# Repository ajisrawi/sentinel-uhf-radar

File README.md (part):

<p align="center">
  <picture>
    <source media="(prefers-color-scheme: dark)" srcset="docs/assets/logo-dark.svg">
    
  </picture>
</p>

<p align="center">
  <b>A complete reference design for a two-face UHF early-warning phased-array radar</b><br>
  system sizing · antenna design and EM simulation · seven KiCad PCB projects · site visualisation
</p>

<p align="center">
  
  <br><sub>AI visualisation (Pixelcut / Nano Banana 2.1) generated from the project's Blender model. Site details are illustrative.</sub>
</p>

---

## Contents

- [What this is](#what-this-is)
- [Key numbers](#key-numbers)
- [Architecture](#architecture)
- [System design](#system-design)
- [Antenna and EM simulation](#antenna-and-em-simulation)
- [Electronics: seven custom boards](#electronics-seven-custom-boards)
- [Site and building](#site-and-building)
- [Cost estimate](#cost-estimate)
- [Repository layout](#repository-layout)
- [Reproduce everything](#reproduce-everything)
- [Verification status and known gaps](#verification-status-and-known-gaps)
- [Notes](#notes)

## What this is

SENTINEL-UHF is an engineering reference design for a ground-based early-warning radar in the class of
PAVE PAWS / UEWR. It is built from public radar engineering principles, and every number in it comes from code in
this repository:

- a **system budget** (aperture, power, detection range, search fence, data rates),
- an **antenna element** sized with a **method-of-moments EM solver** written for the project and validated against
  textbook results, including a 61-element mutual-coupling and scan-impedance study,
- **seven complete KiCad 10 projects** covering every custom board in the radar, each with a schematic, PCB, gerbers
  and its own symbol/footprint library,
- a **Blender model** of the site and a photorealistic visualisation.

It is a first-pass design meant for study and as a starting point. It is not a fielded system and nothing here is
released for fabrication.

## Key numbers

| | |
|---|---|
| Band | 420–450 MHz (UHF radiolocation), circular polarisation |
| Faces | 2 × 120° = 240° azimuth, tilted back 20° |
| Aperture | 22 m active circle per face, **2,587 elements** on a 0.41 m triangular lattice |
| Gain / beamwidth | 39.1 dBi / 1.83° at broadside |
| Peak / average RF | **776 kW / 155 kW per face** (300 W GaN per element, 20 % duty) |
| Detection, 10 m² target | **6,301 km** broadside · 5,951 km at 30° · 3,855 km at 60° (incl. EM mismatch loss) |
| Search fence | 135 beams over 120° × 3°, 10.8 s frame |
| Digital back end | 324 RFSoC tiles per face, 1.03 Tb/s element data → 6.4 Gb/s after beamforming |
| Site prime power | 1.45 MW |

## Architecture

```mermaid
flowchart LR
    A["Crossed-dipole element<br/>× 2,587 per face"] --- FB["Feed board<br/>hybrid + baluns"]
    FB --- TRM["T/R module<br/>300 W GaN, LNA"]
    TRM --- BP["Tile backplane<br/>8 slots, fused 50 V"]
    BP --- TILE["RFSoC tile<br/>9 RX + 9 TX channels"]
    CAL["Calibration network"] --- TRM
    CAL --- TILE
    PSU["Subarray PSU<br/>380 V → 50 V"] --- BP
    CLK["Clock & timing<br/>122.88 MHz, SYSREF, PPS"] --- TILE
    TILE -- "QSFP28 4×25 Gb/s" --> BF["Face beamformer<br/>16 receive beams"]
    BF --> SP["Signal processor<br/>pulse compression, Doppler, CFAR"]
    SP --> DP["Data processor<br/>tracking, discrimination, C2"]
```

Every element has its own T/R module and its own ADC/DAC channel. There is no analog beamforming network: beams are
formed digitally, so one face can hold a search fence and track several targets in the same dwell.

## System design

`radar_sizing.py` sizes the radar from first principles (Skolnik, *Radar Handbook*). The lattice spacing is set so
no grating lobes appear out to 60° scan at 450 MHz. The result, 2,587 elements in 22 m, lands very close to the
fielded PAVE PAWS (2,677 positions in 22.1 m), which is a useful sanity check.

| Waveform | Pulse | Bandwidth | Range resolution | Use |
|---|---|---|---|---|
| Long-range search | 16 ms LFM | 100 kHz | 1.5 km | horizon fence |
| Track | 2–8 ms LFM | 1 MHz | 150 m | track updates |
| Discrimination | 0.25–2 ms LFM | 10 MHz | 15 m | object separation |

## Antenna and EM simulation

Each element is a pair of crossed 12 mm aluminium dipoles, **28 cm long, 18 cm above the
face**, combined in a 90° hybrid for circular polarisation.

The element was designed with `antenna/mom.py`, a thin-wire method-of-moments solver written for this project
(rooftop basis functions, Galerkin testing, image theory for the ground plane, delta-gap ports). It reproduces the
textbook half-wave dipole: **84 + j45 Ω and 2.16 dBi** (theory: 2.15 dBi). `antenna/simulate.py` then solves a
**61-element hexagonal patch** (122 ports, 1,830 unknowns) at 420, 435 and 450 MHz to get the full coupling matrix,
the active reflection coefficient versus scan, and the embedded element pattern.

| Result (centre element) | Value |
|---|---|
| Embedded realised gain, broadside | 4.8 dBi (ideal cell 5.9 dBi) |
| Axial ratio, broadside | 1.3 dB |
| Nearest-neighbour coupling | -19.6 dB |
| Worst active reflection, band × ±60° | -3.4 dB |

> **Where it falls short.** The match holds to about −9 dB out to 45° but drops to about −4 dB at 60°, which costs
> about 2.2 dB per pass at the scan edge (already included in the detection numbers). A lattice trade study
> (`antenna/explore.py`) showed a tighter 0.37 m grid gains under 1 dB, which isn't worth 30 % more modules.
> The next step is a wide-angle matching sheet, checked in a full-wave model that includes the balun and feed posts.

## Electronics: seven custom boards

Every custom board is generated from a Python circuit description (`gen_schematic.py` / `gen_design.py`) and checked by
KiCad itself:

1. **ERC**: electrical rules, 0 violations required.
2. **Netlist intent check**: KiCad's extracted netlist is compared pin-for-pin with the intended circuit.
3. **Layout**: a shared placement / fan-out / A* routing engine (`hardware/tools/pcbgen.py`) lays out the board on 4
   layers (signal / solid ground / power + signal / signal), then KiCad DRC checks it, refills the zones and verifies
   parity with the schematic.

| Board | Per face | Role | Parts | Nets | ERC | Netlist | Layout | Size |
|---|---|---|---|---|---|---|---|---|
| **T/R module** | 2,587 | GaN PA chain, receiver, protection, bias, telemetry | 144 | 90 | 0 | ✔ | ✅ DRC clean | 230 × 152 mm |
| **Element feed board** | 2,587 | 90 deg hybrid, matching, baluns into the crossed dipoles | 19 | 11 | 0 | ✔ | ✅ DRC clean | 86 × 56 mm |
| **RFSoC digitiser tile** | 324 | SOM carrier: 9 RX + 9 TX channels, module links, QSFP28 | 118 | 187 | 0 | ✔ | ✅ DRC clean | 320 × 260 mm |
| **Tile backplane** | 324 | 8 module slots, fused 50 V drain bus, point-to-point control | 57 | 59 | 0 | ✔ | ✅ DRC clean | 232 × 112 mm |
| **Subarray power supply** | 324 | 380 V -> 50 V, two 600 W bricks, supervisor, 2.5 mm HV rules | 56 | 38 | 0 | ✔ | ✅ DRC clean | 300 × 185 mm |
| **Calibration network** | 324 | SPDT selector tree + inject/measure switch on the module CAL ports | 37 | 25 | 0 | ✔ | ✅ DRC clean | 120 × 82 mm |
| **Clock & timing** | 41 | PLL-cleaned 122.88 MHz, SYSREF from PPS, LVDS to 8 tiles | 63 | 82 | 0 | ✔ | ✅ DRC clean | 150 × 130 mm |

7 of 7 layouts are DRC-clean with zero unrouted nets.

### T/R module
`hardware/tr_module/` · 2,587 per face · 144 parts · 90 nets · ✅ DRC clean

📄 [Bill of materials (CSV)](hardware/tr_module/export/SENTINEL_TRM_BOM.csv) · [Schematic (PDF)](hardware/tr_module/export/SENTINEL_TRM_schematic.pdf) · [Gerbers](hardware/tr_module/export/gerbers)

GaN driver + 300 W GaN final, drop-in circulator, 30 dB coupler, two-stage PIN/Schottky limiter, LNA (NF 0.5 dB), SAW filter. Hardware sequencing interlock: the drain switch closes only when `TX_EN` AND gate-bias-OK AND MCU-enable. STM32G031 monitors drain current, VSWR, temperature and both gates.

### Element feed board
`hardware/feed_board/` · 2,587 per face · 19 parts · 11 nets · ✅ DRC clean

📄 [Bill of materials (CSV)](hardware/feed_board/export/SENTINEL_FEED_BOM.csv) · [Schematic (PDF)](hardware/feed_board/export/SENTINEL_FEED_schematic.pdf) · [Gerbers](hardware/feed_board/export/gerbers)

3 dB 90° hybrid for circular polarisation, isolated port into a 100 W load, per-dipole matching from the EM model (x: series 11.2 nH; y: shunt 3.9 pF + series 20.7 nH), 1:1 baluns, static-bleed chokes.

### RFSoC digitiser tile
`hardware/rfsoc_tile/` · 324 per face · 118 parts · 187 nets · ✅ DRC clean

📄 [Bill of materials (CSV)](hardware/rfsoc_tile/export/SENTINEL_TILE_BOM.csv) · [Schematic (PDF)](hardware/rfsoc_tile/export/SENTINEL_TILE_schematic.pdf) · [Gerbers](hardware/rfsoc_tile/export/gerbers)

Carrier for a commercial RFSoC system-on-module: 9 receive channels (SMA → 1:2 balun → ADC), 9 transmit channels (DAC → centre-tapped balun → SMA), eight RS-485 module links, clock input, calibration control, QSFP28 (4 × 25 Gb/s) to the beamformer, 12 V → 3.3 V / 3 A buck. Routed with the EasyEDA Pro autorouter (Top / In2 / Bottom, In1 solid GND) and imported back into KiCad (`tools/import_easyeda.py`, `easyeda_routes.json`).

### Tile backplane
`hardware/backplane/` · 324 per face · 57 parts · 59 nets · ✅ DRC clean

📄 [Bill of materials (CSV)](hardware/backplane/export/SENTINEL_BACKPLANE_BOM.csv) · [Schematic (PDF)](hardware/backplane/export/SENTINEL_BACKPLANE_schematic.pdf) · [Gerbers](hardware/backplane/export/gerbers)

Eight module slots. Each gets a 15 A fuse on the 50 V drain bus and a resettable fuse on 12 V aux. All control lines run point-to-point to one 40-pin cable for the tile, so a faulty module cannot disturb its neighbours.

### Subarray power supply
`hardware/psu/` · 324 per face · 56 parts · 38 nets · ✅ DRC clean

📄 [Bill of materials (CSV)](hardware/psu/export/SENTINEL_PSU_BOM.csv) · [Schematic (PDF)](hardware/psu/export/SENTINEL_PSU_schematic.pdf) · [Gerbers](hardware/psu/export/gerbers)

380 VDC → 50 V: two isolated 600 W full bricks (current-shared, OR-ed), NTC inrush limiter with relay bypass, opto-isolated enables, STM32 supervisor, 12 V aux brick. Pulse energy (87 A for 16 ms) comes from a chassis capacitor bank on M6 studs. Primary nets enforce IPC-2221 2.5 mm clearance through KiCad custom rules.

### Calibration network
`hardware/cal_board/` · 324 per face · 37 parts · 25 nets · ✅ DRC clean

📄 [Bill of materials (CSV)](hardware/cal_board/export/SENTINEL_CAL_BOM.csv) · [Schematic (PDF)](hardware/cal_board/export/SENTINEL_CAL_schematic.pdf) · [Gerbers](hardware/cal_board/export/gerbers)

Binary tree of seven SPDT switches (8 → 1, one select bit per level) plus an inject/measure switch, so the tile can inject into or measure every module's coupler port through one common path.

### Clock & timing
`hardware/clock_board/` · 41 per face · 63 parts · 82 nets · ✅ DRC clean

📄 [Bill of materials (CSV)](hardware/clock_board/export/SENTINEL_CLOCK_BOM.csv) · [Schematic (PDF)](hardware/clock_board/export/SENTINEL_CLOCK_schematic.pdf) · [Gerbers](hardware/clock_board/export/gerbers)

Narrow-loop PLL locks a 122.88 MHz VCXO to the site 10 MHz. SYSREF is PPS re-timed by the clean clock in a D flip-flop, so it is phase-aligned on every tile. Six quad LVDS drivers feed 8 tiles.

## Site and building

`render/build_radar.py` builds the site procedurally in Blender. The building is a 48 m equilateral triangle in plan
with its front corner truncated, 32 m high, with both array faces tilted back 20°. Each 33 m face carries a 28 m
octagon of **4,305 crossed-dipole positions**: the 2,587 active elements in the 22 m circle, plus terminated dummy
elements around them. That ratio (60 % active) is close to PAVE PAWS (1,792 of 2,677).

## Cost estimate

Rough order of magnitude for one two-face site, using commercial GaN and RFSoC prices at production volume:

| Item | Basis | $M |
|---|---|---|
| T/R modules | 5,174 × $4–6k | 21–31 |
| RFSoC tiles | 648 × $8–12k | 5–8 |
| Antenna faces | elements, hybrids, ground plane | 5–9 |
| Beamformer and processors | FPGA + GPU | 10–18 |
| Power and cooling | substation, gensets, chillers | 15–25 |
| Building and site works | 32 m structure, security | 40–80 |
| Software | scheduler, tracking, discrimination, C2 | 40–100 |
| Integration, calibration, test | | 20–40 |
| Engineering and program | | 30–60 |
| **Total acquisition** | | **≈ 186–371** |

Equipment alone is about $56–91M. Military-qualified modules ($10–20k each) and software overruns are the biggest
risks. Operation adds roughly $15–25M per year. The > $1 billion figures quoted for fielded radars include decades
of operation, security and program overhead.

## Repository layout

```
radar_sizing.py            system budget (run it first)
antenna/                   MoM solver, element + 61-element array study, lattice trade study, results/
hardware/
  tools/                   schematic writer, PCB engine, KiCad build / ERC / DRC scripts
  tr_module/               T/R module           (KiCad project + generators + gerbers)
  feed_board/              element feed board
  rfsoc_tile/              RFSoC digitiser tile (SOM carrier)
  backplane/               tile backplane
  psu/                     subarray power supply
  cal_board/               calibration network
  clock_board/             clock & timing distribution
render/                    Blender site model and renders
report/                    interactive HTML design report (build_report.py)
docs/                      logo, README figures, generators
```

Each `hardware/<board>/` folder holds `SENTINEL_*.kicad_pro/.kicad_sch/.kicad_pcb`, its `SENTINEL.kicad_sym` /
`SENTINEL.pretty` libraries, `export/` (schematic PDF, grouped BOM CSV, 3D view, gerbers + drill files) and the generators.

## Reproduce everything

Requires Python 3.13 with numpy, scipy, matplotlib, shapely, pillow and PyMuPDF, plus KiCad 10 and Blender 5.2.

```bash
python radar_sizing.py
cd antenna && python simulate.py && cd ..                              # ~8 min
cd hardware/tr_module && python gen_footprints.py && python gen_schematic.py && cd ../..
bash hardware/tools/sch_check.sh hardware/tr_module SENTINEL_TRM        # ERC + netlist check + footprint dump
python hardware/tr_module/pcb_plan.py                                  # place + route (~30-60 min)
bash hardware/tools/pcb_check.sh hardware/tr_module SENTINEL_TRM        # build board, DRC, 3D view, gerbers
bash hardware/tools/export_bom.sh                                      # grouped BOM CSV for every board
# same pattern for the other boards (gen_design.py, then the two check scripts)
blender -b -P render/build_radar.py -- night 64
python report/build_report.py && python docs/make_figures.py && python docs/make_readme.py
```

## Verification status and known gaps

| Item | Status |
|---|---|
| System budget | ✅ cross-checked against public PAVE PAWS figures |
| MoM solver | ✅ validated on the half-wave dipole |
| Element + array EM model | ✅ 61 elements, 3 frequencies, full coupling (thin-wire, infinite ground) |
| Wide-angle match | ⚠️ ~−4 dB at 60°: needs a WAIM sheet and full-wave verification |
| All 7 schematics | ✅ 0 ERC violations, exact netlist match |
| PCB layouts | 7/7 DRC-clean; the rest are being routed |
| Differential pairs | ⚠️ data-converter, LVDS and 25 Gb/s pairs are auto-routed as single nets; need a manual coupled, length-matched pass |
| Pin maps not in the KiCad library | ⚠️ RFSoC SOM connector, PLL and RF modules use this project's own pin maps; map to the chosen parts' datasheets |
| T/R module matching values | ⚠️ first-pass from device models; tune on a load-pull bench |
| Thermal | ⚠️ 45 W average per module on a cold plate; needs CFD and a test article |

## Notes

- **No license.** This repository is published without a license. All rights are reserved by the author; viewing
  is fine, but reuse needs permission.
- Designed with [Claude Code](https://claude.com/claude-code). The radar is a study design built from public
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
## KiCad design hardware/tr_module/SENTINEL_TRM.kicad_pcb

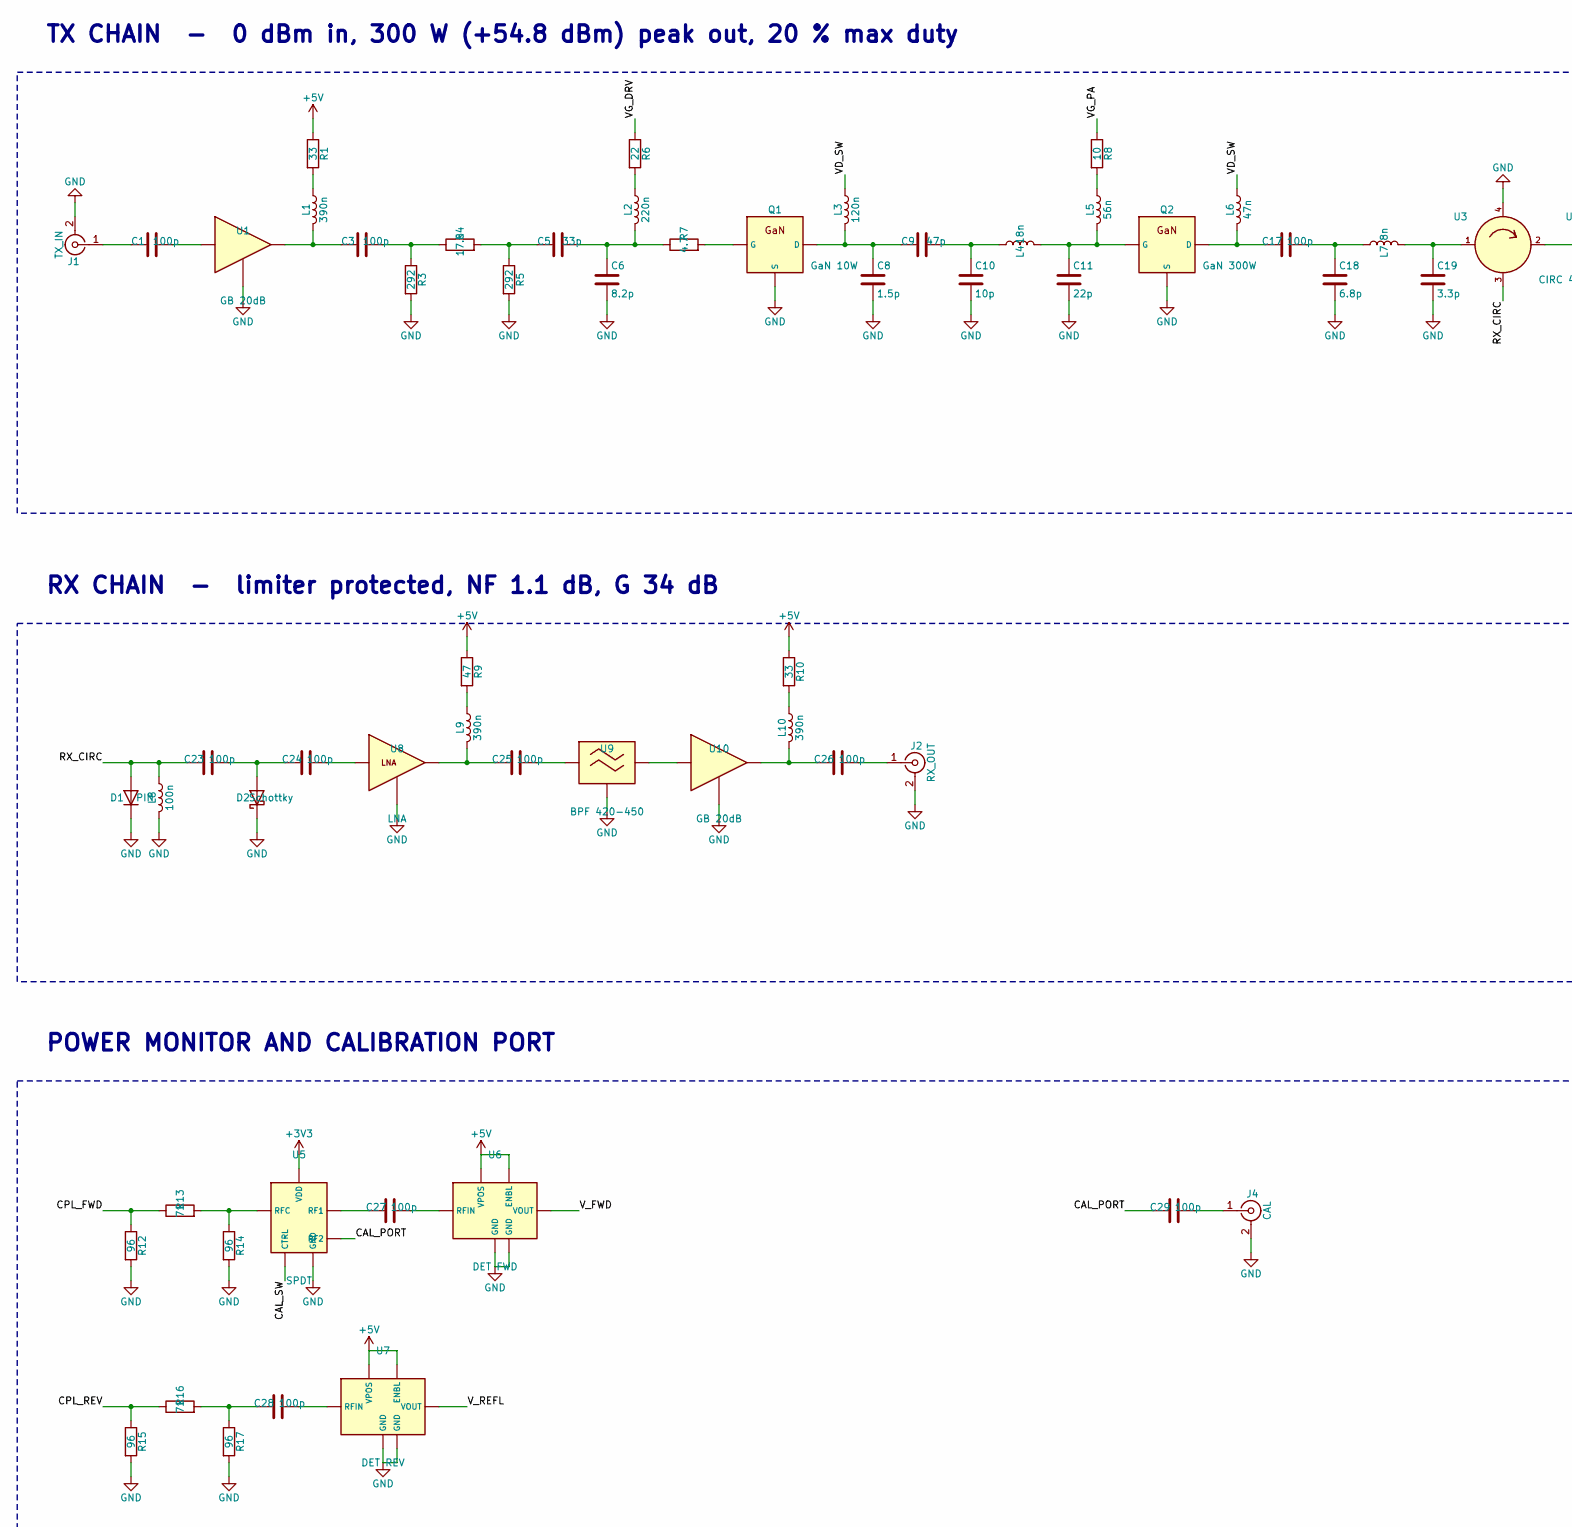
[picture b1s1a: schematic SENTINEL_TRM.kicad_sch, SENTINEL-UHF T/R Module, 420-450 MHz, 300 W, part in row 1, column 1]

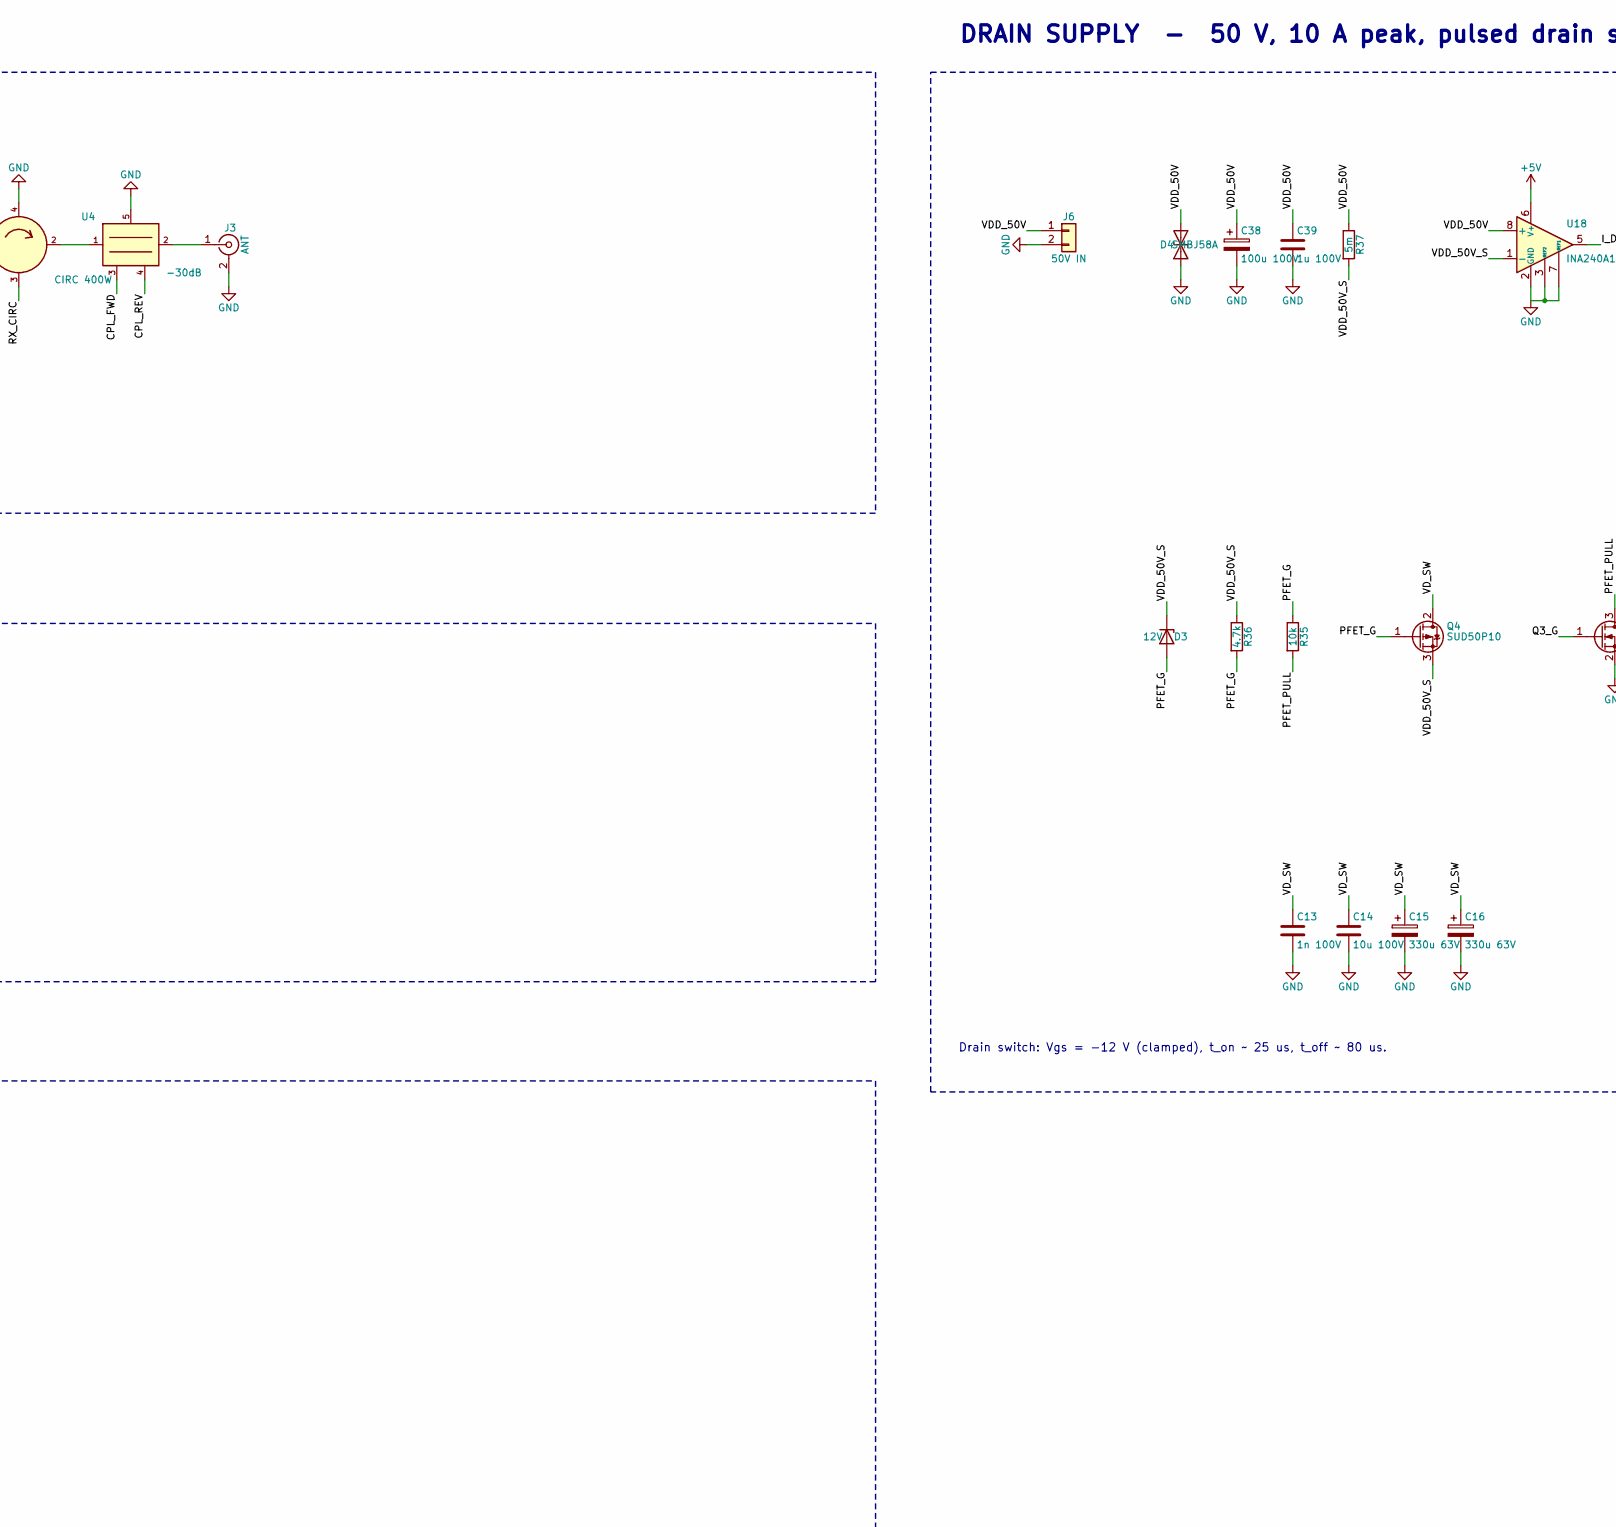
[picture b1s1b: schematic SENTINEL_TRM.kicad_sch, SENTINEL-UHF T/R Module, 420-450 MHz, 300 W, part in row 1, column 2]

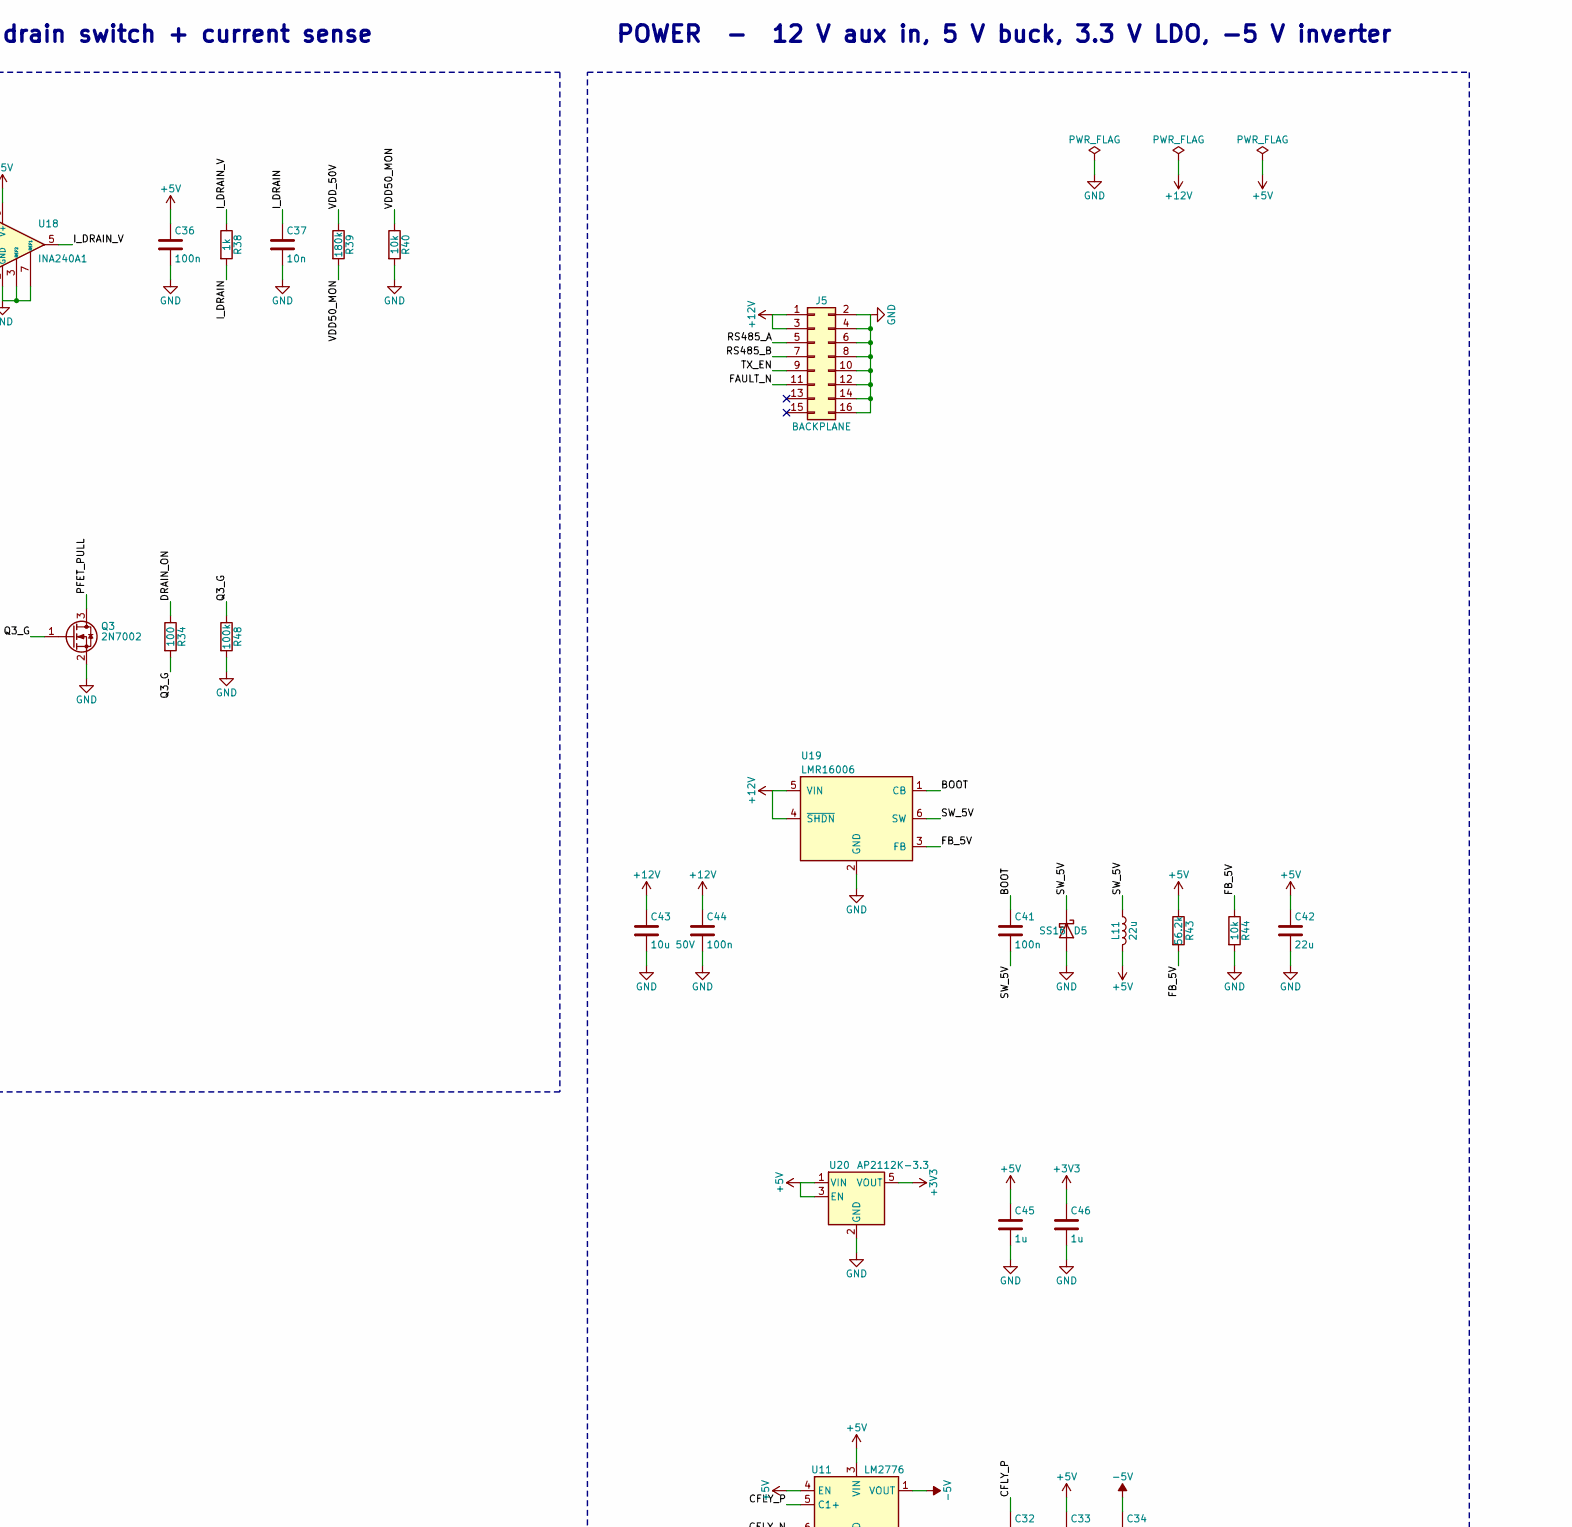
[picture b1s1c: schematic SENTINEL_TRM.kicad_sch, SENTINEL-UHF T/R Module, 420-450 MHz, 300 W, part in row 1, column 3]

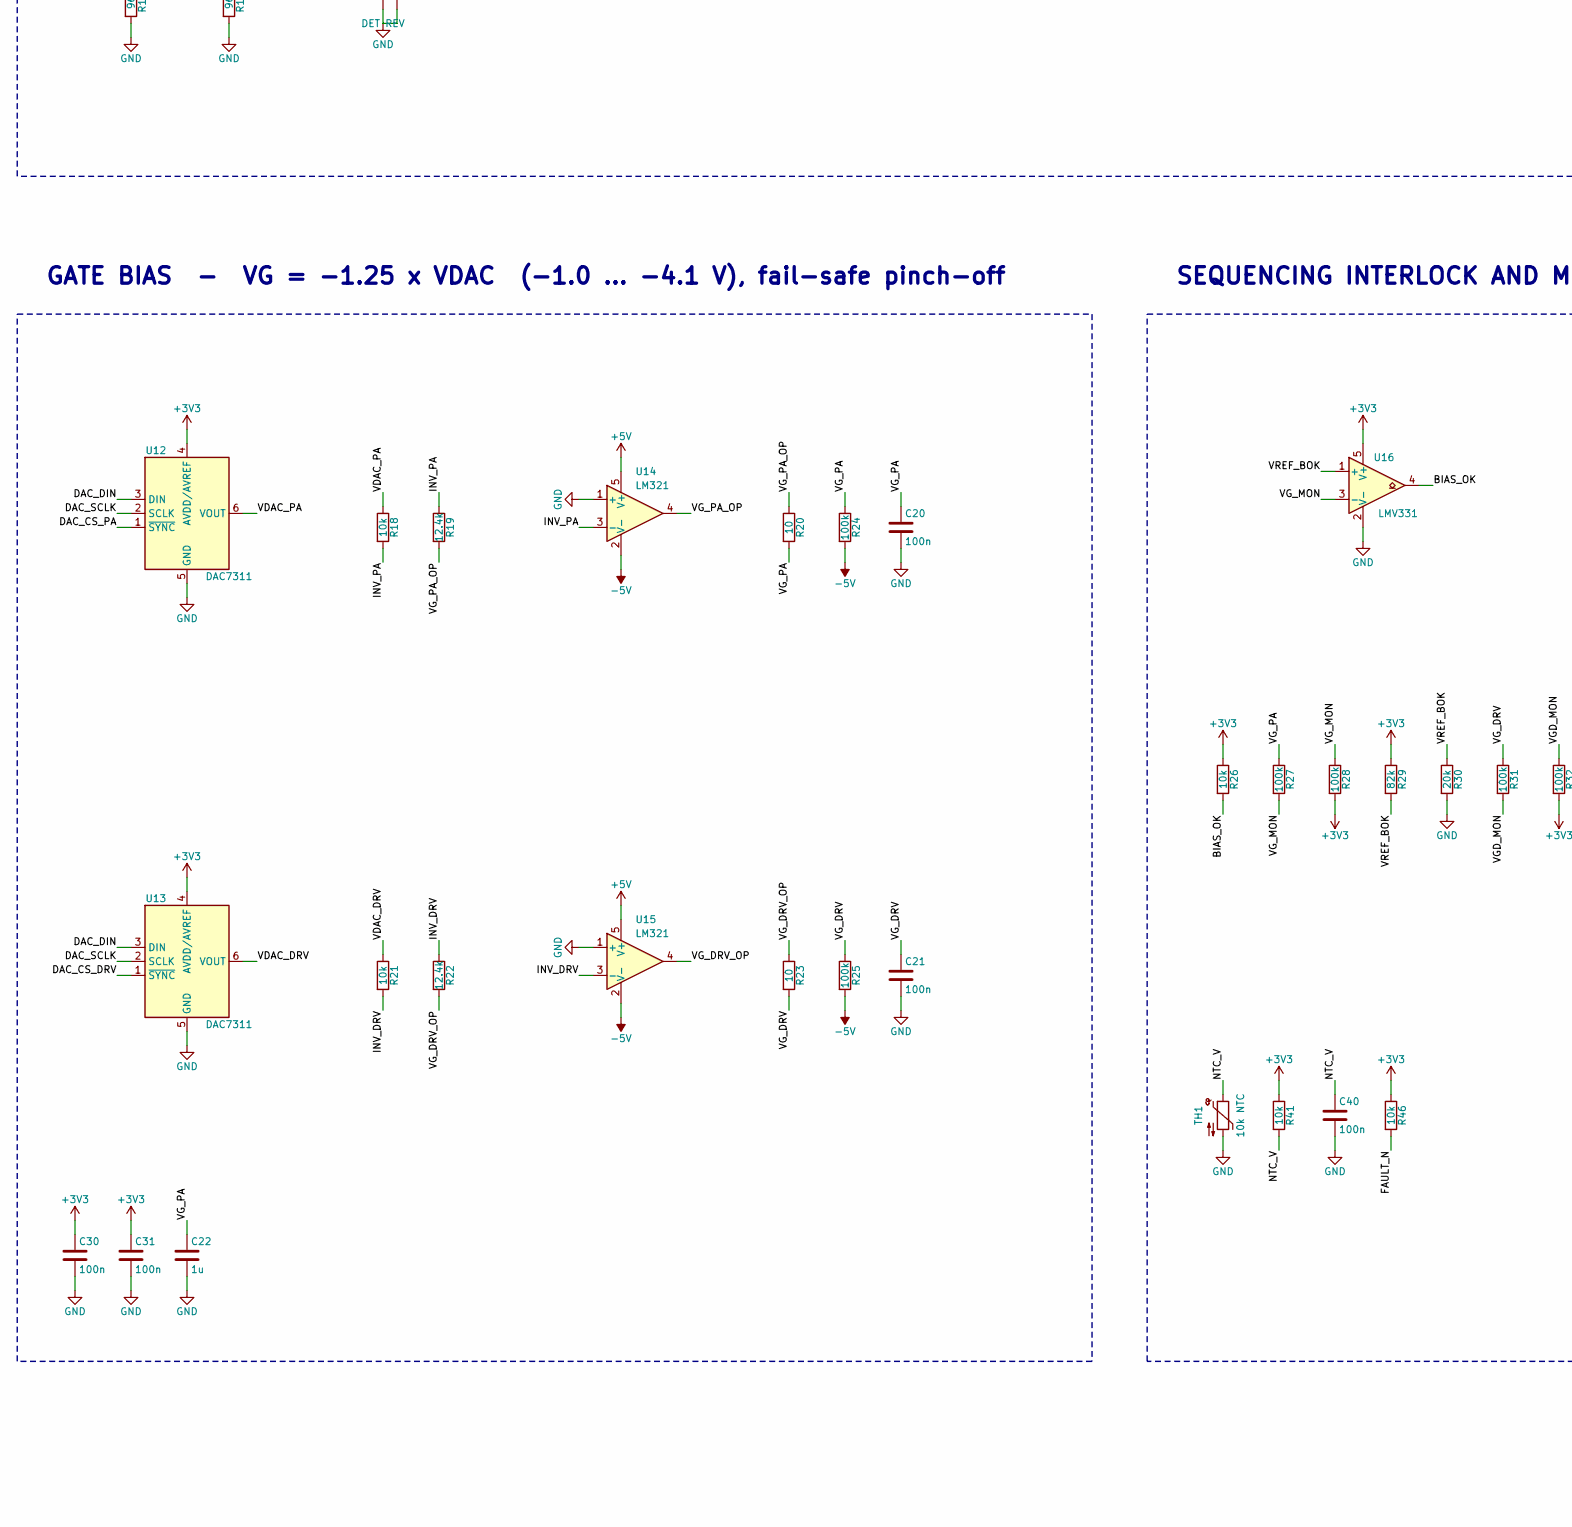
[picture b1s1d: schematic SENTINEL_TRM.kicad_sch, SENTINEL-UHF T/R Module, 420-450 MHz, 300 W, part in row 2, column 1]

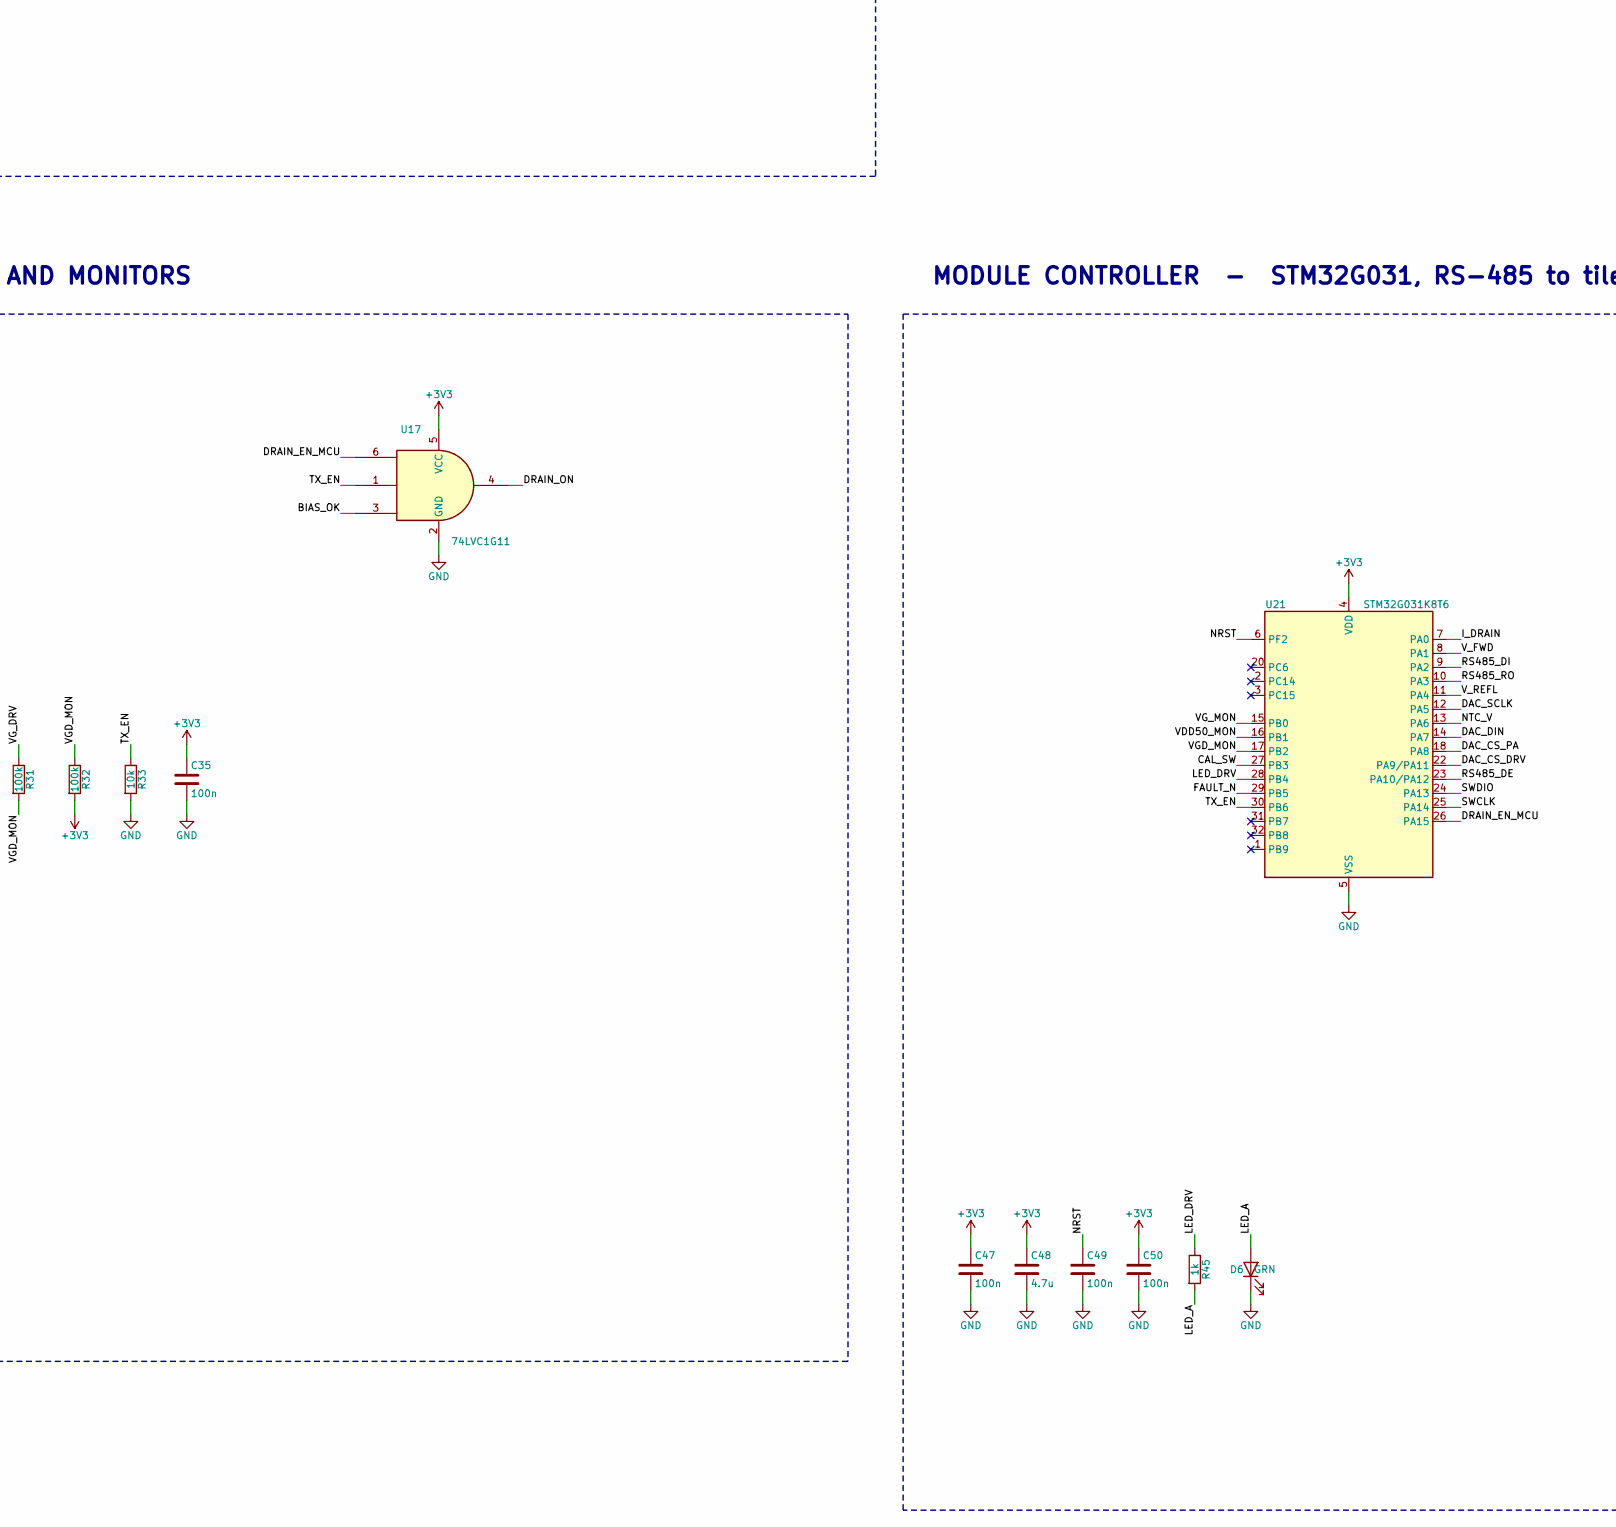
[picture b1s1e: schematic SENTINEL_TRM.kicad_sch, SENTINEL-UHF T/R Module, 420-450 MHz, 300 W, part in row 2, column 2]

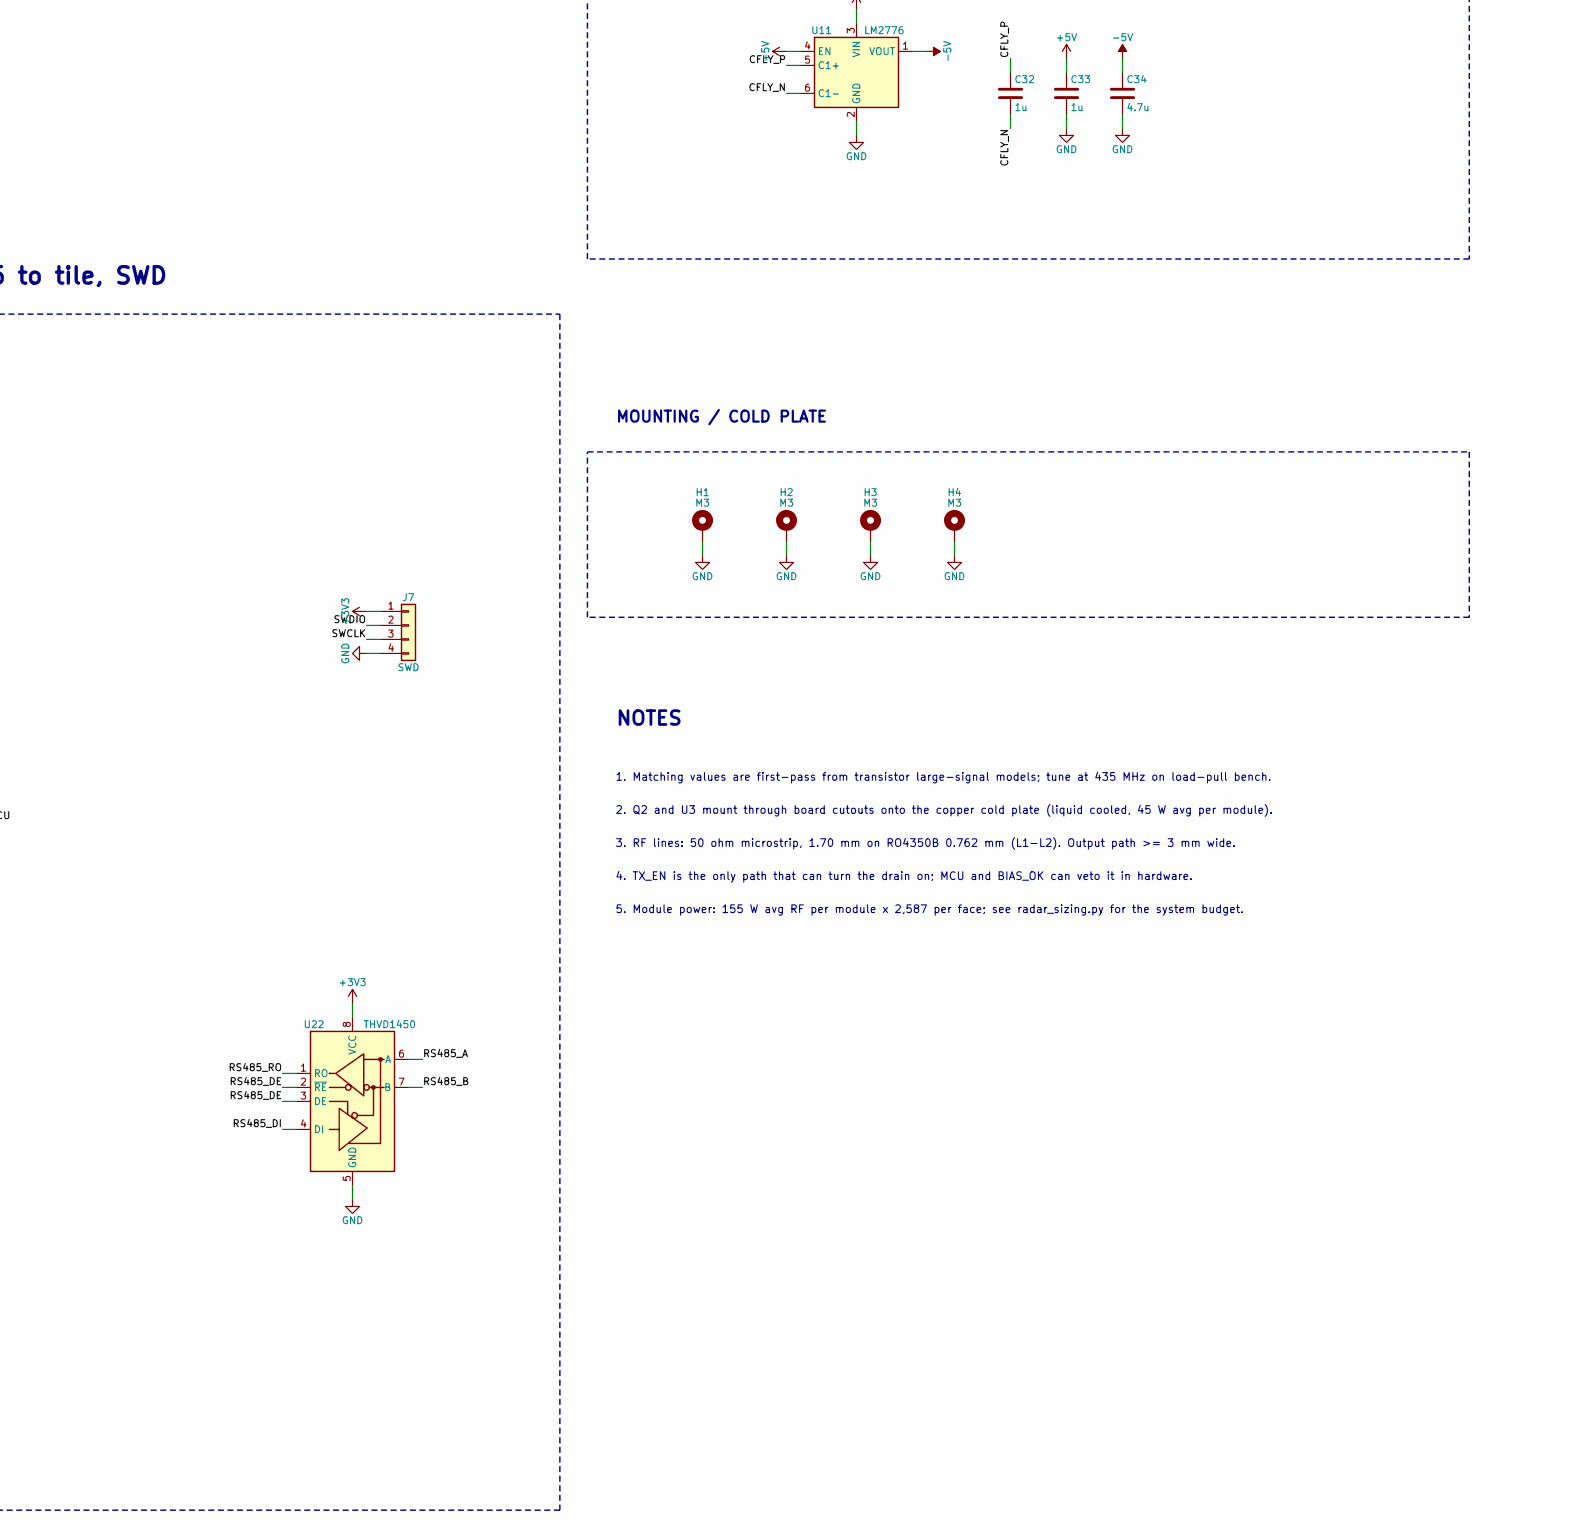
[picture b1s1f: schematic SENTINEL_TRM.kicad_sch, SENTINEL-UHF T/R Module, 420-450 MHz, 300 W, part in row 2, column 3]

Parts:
C1, C3, C23, C24, C25, C26, C27, C28, C29: 100p; C_0603_1608Metric
C5: 33p; C_0603_1608Metric
C6: 8.2p; C_0603_1608Metric
C8: 1.5p; C_0805_2012Metric
C9: 47p; C_0805_2012Metric
C10: 10p; C_0805_2012Metric
C11: 22p; C_1206_3216Metric
C13: 1n 100V; C_1210_3225Metric
C14: 10u 100V; C_2220_5750Metric
C15, C16: 330u 63V; CP_Elec_10x10.5
C17: 100p; C_2220_5750Metric
C18: 6.8p; C_2220_5750Metric
C19: 3.3p; C_2220_5750Metric
C20, C21, C30, C31, C35, C36, C40, C41, C44, C47, C49, C50: 100n; C_0603_1608Metric
C22, C32, C33, C45, C46: 1u; C_0603_1608Metric
C34: 4.7u; C_0805_2012Metric
C37: 10n; C_0603_1608Metric
C38: 100u 100V; CP_Elec_10x10.5
C39: 1u 100V; C_1210_3225Metric
C42: 22u; C_1210_3225Metric
C43: 10u 50V; C_1210_3225Metric
C48: 4.7u; C_0603_1608Metric
D1: PIN; D_SMB
D2: Schottky; D_SOD-323
D3: 12V; D_SOD-323
D4: SMBJ58A; D_SMB
D5: SS16; D_SMA
D6: GRN; LED_0603_1608Metric
H1, H2, H3, H4: M3; MountingHole_3.2mm_M3_Pad
J1: TX_IN; SMA_Amphenol_132289_EdgeMount
J2: RX_OUT; SMA_Amphenol_132289_EdgeMount
J3: ANT; N_EdgeLaunch
J4: CAL; SMA_Amphenol_132289_EdgeMount
J5: BACKPLANE; PinHeader_2x08_P2.54mm_Vertical
J6: 50V IN; Molex_Mini-Fit_Jr_5566-02A_2x01_P4.20mm_Vertical
J7: SWD; PinHeader_1x04_P2.54mm_Vertical
L1, L9, L10: 390n; L_0603_1608Metric
L2: 220n; L_0805_2012Metric
L3: 120n; L_1210_3225Metric
L4: 18n; L_0805_2012Metric
L5: 56n; L_1210_3225Metric
L6: 47n; L_1812_4532Metric
L7: 8n; L_1812_4532Metric
L8: 100n; L_0603_1608Metric
L11: 22u; L_1210_3225Metric
Q1: GaN 10W; GaN_Flange_440166; MPN CG2H40010F class
Q2: GaN 300W; GaN_Flange_780; MPN UHF radar GaN, 300 W class
Q3: 2N7002; SOT-23
Q4: SUD50P10; TO-252-2
R1, R10: 33; R_0603_1608Metric
R3, R5: 292; R_0603_1608Metric
R4: 17.6; R_0603_1608Metric
R6: 22; R_0603_1608Metric
R7: 4.7; R_0603_1608Metric
R8: 10; R_0805_2012Metric
R9: 47; R_0603_1608Metric
R12, R14, R15, R17: 96; R_0603_1608Metric
R13, R16: 71; R_0603_1608Metric
R18, R21, R26, R33, R40, R41, R44, R46: 10k; R_0603_1608Metric
R19, R22: 12.4k; R_0603_1608Metric
R20, R23: 10; R_0603_1608Metric
R24, R25, R27, R28, R31, R32, R48: 100k; R_0603_1608Metric
R29: 82k; R_0603_1608Metric
R30: 20k; R_0603_1608Metric
R34: 100; R_0603_1608Metric
R35: 10k; R_1206_3216Metric
R36: 4.7k; R_0805_2012Metric
R37: 5m; R_2512_6332Metric
R38, R45: 1k; R_0603_1608Metric
R39: 180k; R_0603_1608Metric
R43: 56.2k; R_0603_1608Metric
TH1: 10k NTC; R_0603_1608Metric
U1: GB 20dB; SOT-89-3; MPN PHA-13LN+ class
U3: CIRC 400W; Circulator_DropIn_32mm
U4: -30dB; DirCoupler_SMD_12x6
U5: SPDT; SOT-363_SC-70-6
U6: DET FWD; SOT-23-6
U7: DET REV; SOT-23-6
U8: LNA; SOT-89-3
U9: BPF 420-450; BPF_SMD_5x5
U10: GB 20dB; SOT-89-3
U11: LM2776; SOT-23-6
U12, U13: DAC7311; SOT-363_SC-70-6
U14, U15: LM321; SOT-23-5
U16: LMV331; SOT-23-5
U17: 74LVC1G11; SOT-363_SC-70-6
U18: INA240A1; SOIC-8_3.9x4.9mm_P1.27mm
U19: LMR16006; SOT-23-6
U20: AP2112K-3.3; SOT-23-5
U21: STM32G031K8T6; LQFP-32_7x7mm_P0.8mm
U22: THVD1450; SOIC-8_3.9x4.9mm_P1.27mm

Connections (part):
+3V3: C30.1, C31.1, C35.1, C46.1, C47.1, C48.1, C50.1, J7.1, R26.1, R28.2, R29.1, R32.2, R41.1, R46.1, U5.6 (VDD), U12.4 (AVDD/AVREF), U13.4 (AVDD/AVREF), U16.5 (V+), U17.5 (VCC), U20.5 (VOUT), U21.4 (VDD), U22.8 (VCC)
+5V: C33.1, C36.1, C42.1, C45.1, L11.2, R1.1, R9.1, R10.1, R43.1, U6.3 (ENBL), U6.5 (VPOS), U7.3 (ENBL), U7.5 (VPOS), U11.3 (VIN), U11.4 (EN), U14.5 (V+), U15.5 (V+), U18.6 (V+), U20.1 (VIN), U20.3 (EN)
+12V: C43.1, C44.1, J5.1, J5.3, U19.4 (~SHDN), U19.5 (VIN)
-5V: C34.1, R24.2, R25.2, U11.1 (VOUT), U14.2 (V-), U15.2 (V-)
BIAS_OK: R26.2, U16.4, U17.3
BOOT: C41.1, U19.1 (CB)
CAL_PORT: C29.1, U5.3 (RF2)
CAL_SW: U5.4 (CTRL), U21.27 (PB3)
CFLY_N: C32.2, U11.6 (C1-)
CFLY_P: C32.1, U11.5 (C1+)
CPL_FWD: R12.1, R13.1, U4.3 (CPL)
CPL_REV: R15.1, R16.1, U4.4 (ISO)
DAC_CS_DRV: U13.1 (~SYNC), U21.22 (PA9/PA11)
DAC_CS_PA: U12.1 (~SYNC), U21.18 (PA8)
DAC_DIN: U12.3 (DIN), U13.3 (DIN), U21.14 (PA7)
DAC_SCLK: U12.2 (SCLK), U13.2 (SCLK), U21.12 (PA5)
DRAIN_EN_MCU: U17.6, U21.26 (PA15)
DRAIN_ON: R34.1, U17.4
FAULT_N: J5.11, R46.2, U21.29 (PB5)
FB_5V: R43.2, R44.1, U19.3 (FB)
GND: C6.2, C8.2, C10.2, C11.2, C13.2, C14.2, C15.2, C16.2, C18.2, C19.2, C20.2, C21.2, C22.2, C30.2, C31.2, C33.2, C34.2, C35.2, C36.2, C37.2, C38.2, C39.2, C40.2, C42.2, C43.2, C44.2, C45.2, C46.2, C47.2, C48.2, C49.2, C50.2, D1.1 (K), D2.1 (K), D4.1 (A1), D5.2 (A), D6.1 (K), H1.1, H2.1, H3.1, H4.1, J1.2 (Ext), J2.2 (Ext), J3.2 (Ext), J4.2 (Ext), J5.2, J5.4, J5.6, J5.8, J5.10, J5.12, J5.14, J5.16, J6.2, J7.4, L8.2, Q1.3 (S), Q2.3 (S), Q3.2 (S), R3.2, R5.2, R12.2, R14.2, R15.2, R17.2, R30.2, R33.2, R40.2, R44.2, R48.2, TH1.2, U1.2 (GND), U3.4 (GND), U4.5 (GND), U5.2 (GND), U6.2 (GND), U6.6 (GND), U7.2 (GND), U7.6 (GND), U8.2 (GND), U9.2 (GND)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
INV_DRV: R21.2, R22.1, U15.3 (-)
INV_PA: R18.2, R19.1, U14.3 (-)
I_DRAIN: C37.1, R38.2, U21.7 (PA0)
I_DRAIN_V: R38.1, U18.5
LED_A: D6.2 (A), R45.2
LED_DRV: R45.1, U21.28 (PB4)
NRST: C49.1, U21.6 (PF2)
NTC_V: C40.1, R41.2, TH1.1, U21.13 (PA6)
unnamed: C3.2, R3.1, R4.1
unnamed: C5.1, R4.2, R5.1
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
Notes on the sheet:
TX CHAIN - 0 dBm in, 300 W (+54.8 dBm) peak out, 20 % max duty
RX CHAIN - limiter protected, NF 1.1 dB, G 34 dB
POWER MONITOR AND CALIBRATION PORT
DRAIN SUPPLY - 50 V, 10 A peak, pulsed drain switch + current sense
Drain switch: Vgs = -12 V (clamped), t_on ~ 25 us, t_off ~ 80 us.
POWER - 12 V aux in, 5 V buck, 3.3 V LDO, -5 V inverter
GATE BIAS - VG = -1.25 x VDAC (-1.0 ... -4.1 V), fail-safe pinch-off
SEQUENCING INTERLOCK AND MONITORS
MODULE CONTROLLER - STM32G031, RS-485 to tile, SWD
MOUNTING / COLD PLATE
NOTES
1. Matching values are first-pass from transistor large-signal models; tune at 435 MHz on load-pull bench.
2. Q2 and U3 mount through board cutouts onto the copper cold plate (liquid cooled, 45 W avg per module).
3. RF lines: 50 ohm microstrip, 1.70 mm on RO4350B 0.762 mm (L1-L2). Output path >= 3 mm wide.
4. TX_EN is the only path that can turn the drain on; MCU and BIAS_OK can veto it in hardware.
5. Module power: 155 W avg RF per module x 2,587 per face; see radar_sizing.py for the system budget.
